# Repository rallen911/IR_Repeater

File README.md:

# IR_Repeater
The intent of this project is to create a complete solution for home theater installations where the AV equipment is installed such that line-of-sight IR signals are unable to reach them.

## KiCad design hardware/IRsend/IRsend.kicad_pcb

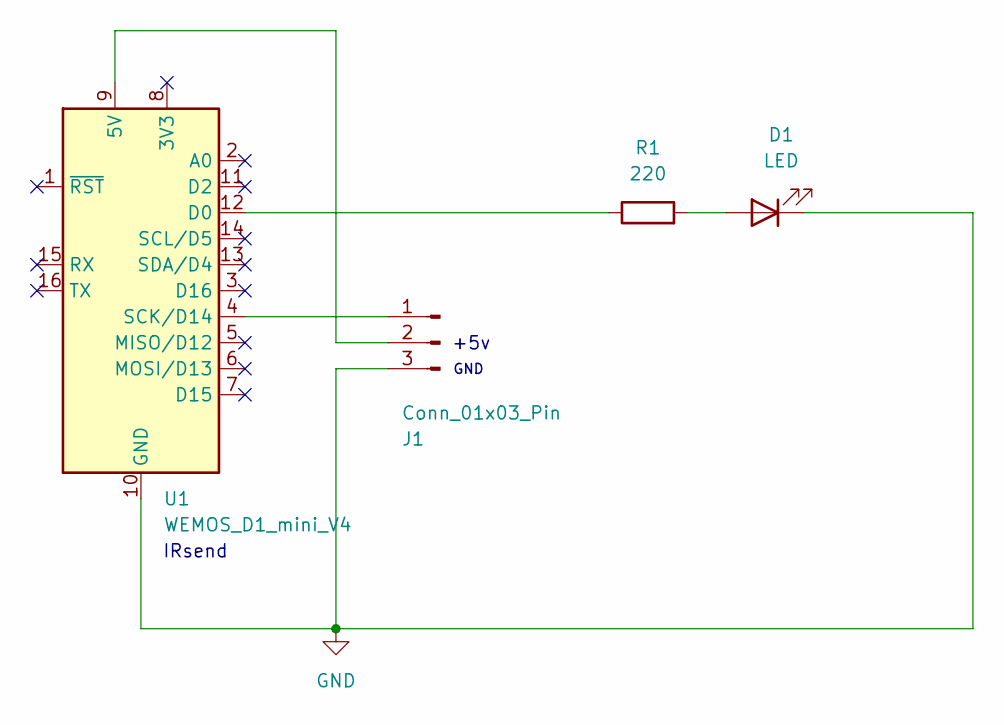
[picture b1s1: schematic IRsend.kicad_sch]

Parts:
D1: LED; LED_D5.0mm
J1: Conn_01x03_Pin; PinSocket_1x03_P2.54mm_Vertical
R1: 220; R_Axial_DIN0207_L6.3mm_D2.5mm_P7.62mm_Horizontal
U1: WEMOS_D1_mini_V4; WEMOS_D1_mini_light

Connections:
GND: D1.1 (K), J1.3, U1.10 (GND)
unnamed: D1.2 (A), R1.2
unnamed: J1.1, U1.4 (SCK/D14)
unnamed: J1.2, U1.9 (5V)
unnamed: R1.1, U1.12 (D0)

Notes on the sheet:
IRsend
GND
+5v

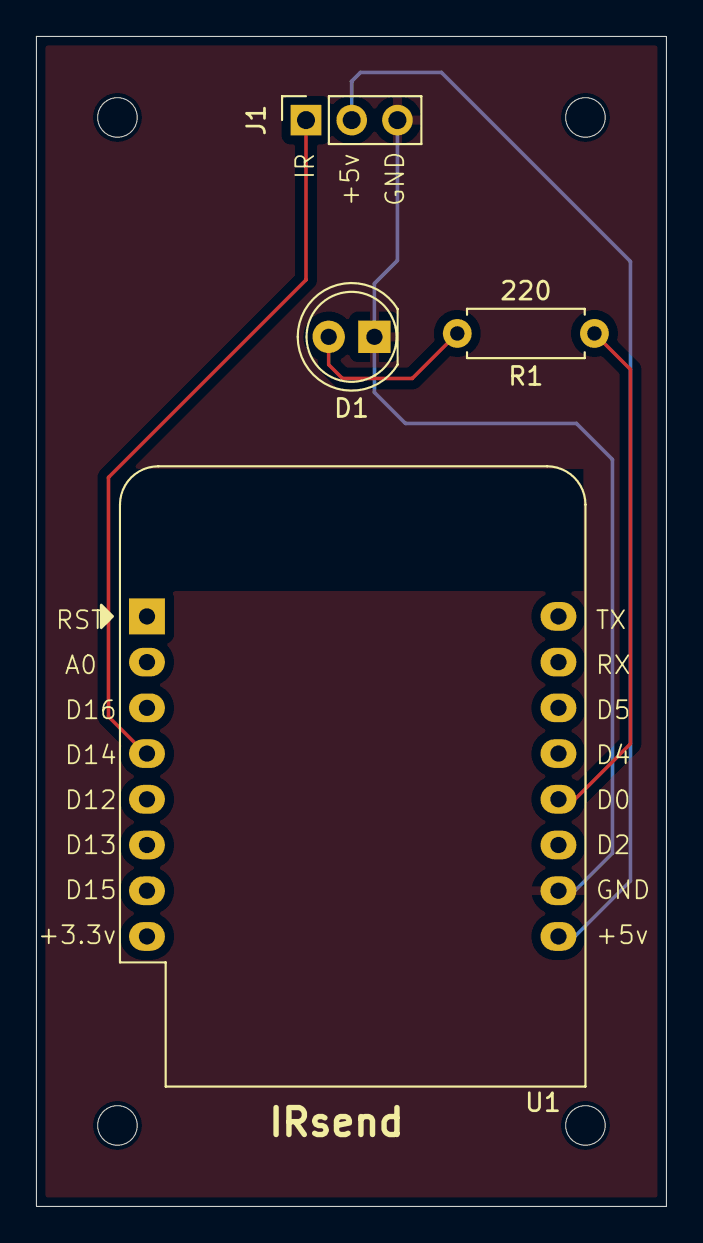
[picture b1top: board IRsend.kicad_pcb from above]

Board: 2 copper layers, 35.0 x 65.0 mm, 4 parts (0 on the bottom side), 5 nets.

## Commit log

2025-03-01 First commit of IRrecv
2025-03-01 First commit of IRsend
2025-03-01 Added .vscode\extensions.json to .gitignore files.
2025-03-08 Update to make the code compatible with ESP8266 WeMOS D1 mini.
2025-03-22 Initial commit of circuit card data.
2025-03-24 Added heartbeat feature where, an LED will extinguish if contact is lost with the peer channel.
2025-04-25 Shortened comms timeout from 10 sec to 5 sec.
2025-04-25 Added IRsend.step to KiCad project.
2025-05-01 Fixed problem with IR signal and GND being swapped on J1.
2025-05-02 Added files for 3D printed case and lid.
2025-05-04 Created new package to upload to PCBWay.
